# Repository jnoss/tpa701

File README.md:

# tpa701
TPA701 board - based off of David A. Mellis' DIY Devices

This is a singe copy of the amplifier, and also changed to take differential input

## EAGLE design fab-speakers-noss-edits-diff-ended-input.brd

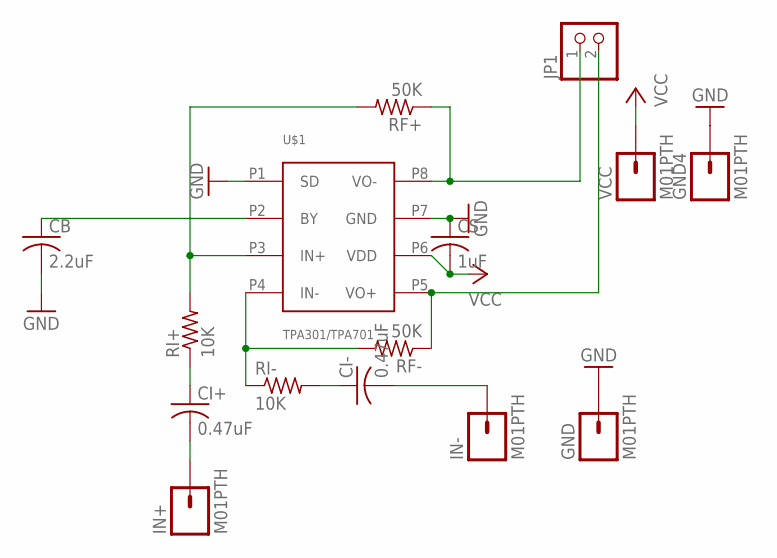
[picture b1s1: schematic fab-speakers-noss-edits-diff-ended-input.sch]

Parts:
CB: 2.2uF; C0603
CI+: 0.47uF; C0603
CI-: 0.47uF; C0603
CS: 1uF; C0603
GND, GND4: M01PTH; 1X01
IN+: M01PTH; 1X01
IN-: M01PTH; 1X01
JP1: PINHD-1X2; 1X02
RF+: 50K; R0603
RF-: 50K; R0603
RI+: 10K; R0603
RI-: 10K; R0603
U$1: TPA301/TPA701; SOIC8
VCC: M01PTH; 1X01

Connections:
GND: CB.2, CS.1, GND.1, GND4.1, U$1.P1 (SD), U$1.P7 (GND)
IN+: CI+.2, IN+.1
IN-: CI-.2, IN-.1
unnamed: RF+.2, RI+.2, U$1.P3 (IN+)
unnamed: CI-.1, RI-.2
unnamed: CI+.1, RI+.1
unnamed: RF-.2, RI-.1, U$1.P4 (IN-)
unnamed: CB.1, U$1.P2 (BY)
O+: JP1.2, RF-.1, U$1.P5 (VO+)
O-: JP1.1, RF+.1, U$1.P8 (VO-)
VCC: CS.2, U$1.P6 (VDD), VCC.1

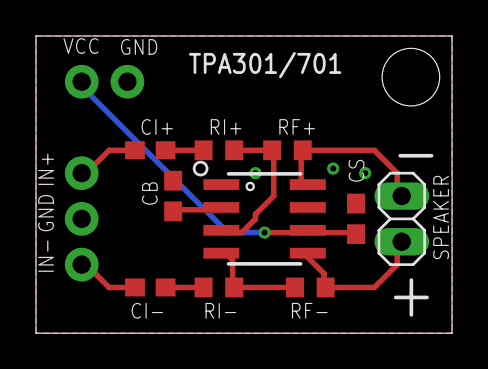
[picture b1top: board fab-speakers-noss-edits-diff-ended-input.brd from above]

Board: 2 copper layers, 23.1 x 16.5 mm, 16 parts (1 on the bottom side), 11 nets.

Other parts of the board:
U$3: OSHW-LOGO-S

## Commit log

2017-01-02 initial
2017-01-02 add diff ended board
2017-01-02 edit typo
2017-01-03 add 2nd supply cap
2017-01-03 add polygon
2017-01-03 fix labels
2017-01-11 add stencil
2017-01-22 add stencils with shrunken pads
2017-01-24 edit stencils

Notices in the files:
parts and their libraries:
SparkFun-Connectors: Licensing: CC v3.0 Share-Alike You are welcome to use this library for commercial purposes.
